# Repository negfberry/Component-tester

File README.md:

# Component-tester
Component tester for Arduino:

For documentation, see the Wiki.

Test many types of semiconductors, resistors, capacitors, inductors, etc.

Full list:

Resistors

Capacitors

Inductors

Diodes

Double diodes - common a/c, series, and inverse-parallel

Zener diodes

BJTs (Bipolar Junction Transistors):

    Regular
  
    Darlington pair
  
FETs:

    JFET
  
    MOSFET:
  
        enhancement mode
    
        depletion mode
    
IGBTs (Insulated Gate Bipolar Transistor)

Triacs

Thyristors

Based on Ardutester and earlier works. Uses the ButtonCtl Arduino library (in my Github). Includes hardware design schematic and PCB layout in Eagle format.
The DUT inputs are relay protected against charged capacitors being inserted.
Do not connect batteries or super capacitors.

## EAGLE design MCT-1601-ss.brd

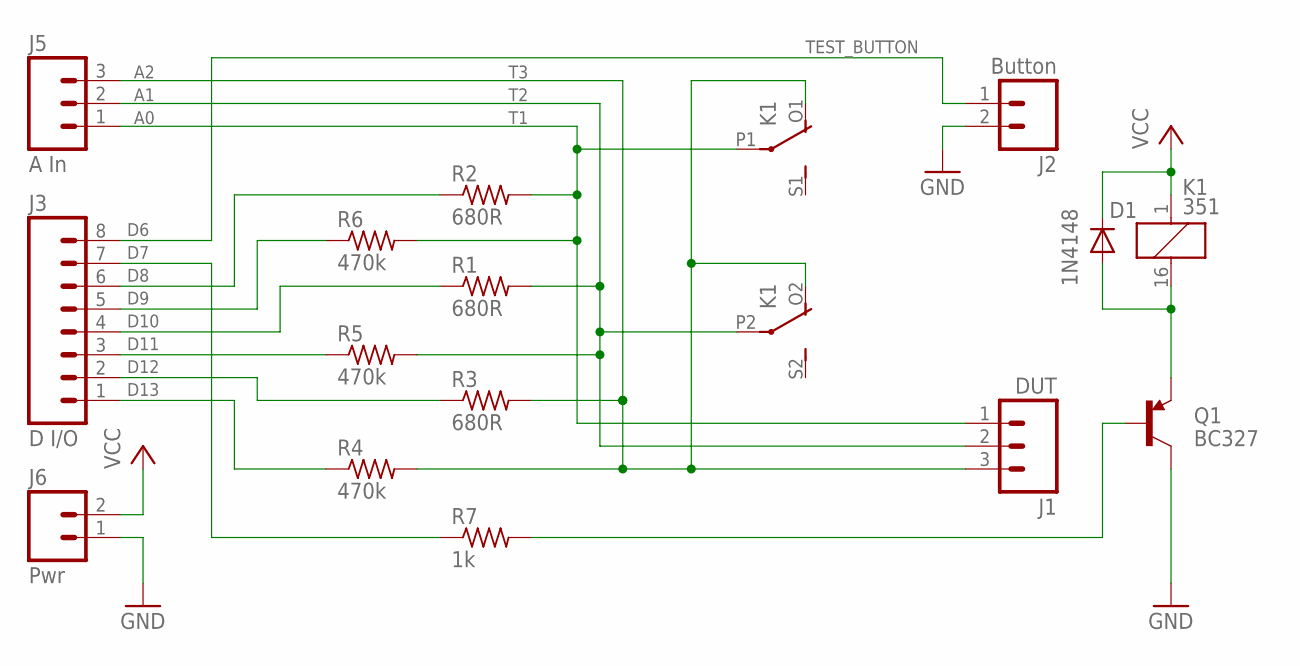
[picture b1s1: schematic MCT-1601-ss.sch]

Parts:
D1: 1N4148; D-2.5
J1: DUT; 1X03
J2: Button; 1X02
J3: D I/O; 1X08_ROUND
J5: A In; 1X03
J6: Pwr; 1X02
K1: 351
Q1: BC327; TO-92
R1, R2, R3: 680R; 0204/5
R4, R5, R6: 470k; 0204/5
R7: 1k; 0204/5

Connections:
D7: J3.7, R7.1
D8: J3.6, R2.1
D9: J3.5, R6.1
D10: J3.4, R1.1
D11: J3.3, R5.1
D12: J3.2, R3.1
D13: J3.1, R4.1
GND: J2.2, J6.1, Q1.3 (C)
unnamed: Q1.2 (B), R7.2
unnamed: D1.A, K1.16 (2), Q1.1 (E)
T1: J1.1, J5.1, K1.P1, R2.2, R6.2
T2: J1.2, J5.2, K1.P2, R1.2, R5.2
T3: J1.3, J5.3, K1.O1 (O), K1.O2 (O), R3.2, R4.2
TEST_BUTTON: J2.1, J3.8
VCC: D1.C, J6.2, K1.1

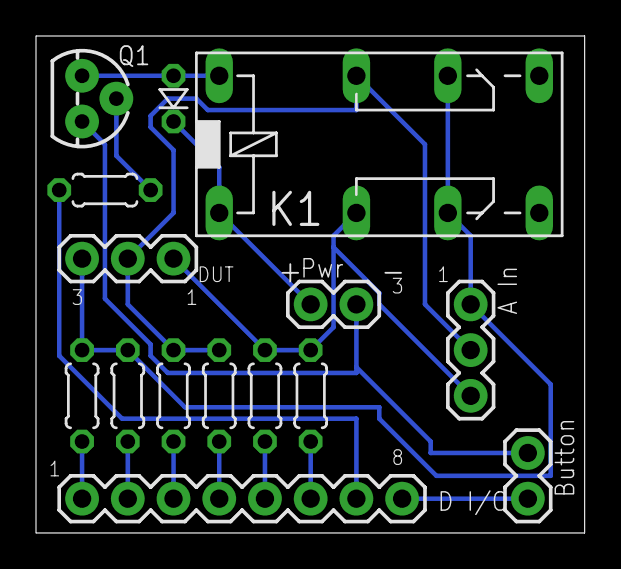
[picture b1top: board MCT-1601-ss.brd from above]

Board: 2 copper layers, 30.5 x 27.6 mm, 15 parts (0 on the bottom side), 15 nets.

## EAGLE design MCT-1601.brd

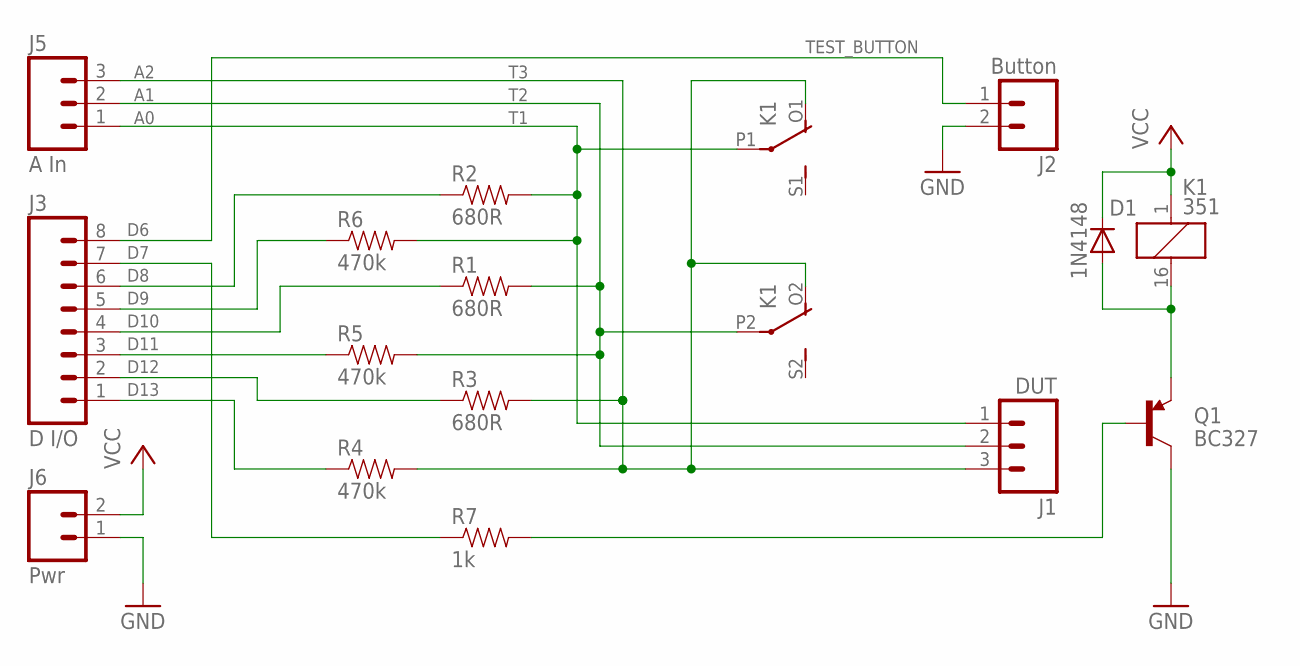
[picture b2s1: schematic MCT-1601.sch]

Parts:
D1: 1N4148; D-2.5
J1: DUT; 1X03
J2: Button; 1X02
J3: D I/O; 1X08_ROUND
J5: A In; 1X03
J6: Pwr; 1X02
K1: 351
Q1: BC327; TO-92
R1, R2, R3: 680R; AXIAL-0.1
R4, R5, R6: 470k; AXIAL-0.1
R7: 1k; AXIAL-0.1

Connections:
D7: J3.7, R7.P$1 (1)
D8: J3.6, R2.P$1 (1)
D9: J3.5, R6.P$1 (1)
D10: J3.4, R1.P$1 (1)
D11: J3.3, R5.P$1 (1)
D12: J3.2, R3.P$1 (1)
D13: J3.1, R4.P$1 (1)
GND: J2.2, J6.1, Q1.3 (C)
unnamed: Q1.2 (B), R7.P$2 (2)
unnamed: D1.A, K1.16 (2), Q1.1 (E)
T1: J1.1, J5.1, K1.P1, R2.P$2 (2), R6.P$2 (2)
T2: J1.2, J5.2, K1.P2, R1.P$2 (2), R5.P$2 (2)
T3: J1.3, J5.3, K1.O1 (O), K1.O2 (O), R3.P$2 (2), R4.P$2 (2)
TEST_BUTTON: J2.1, J3.8
VCC: D1.C, J6.2, K1.1

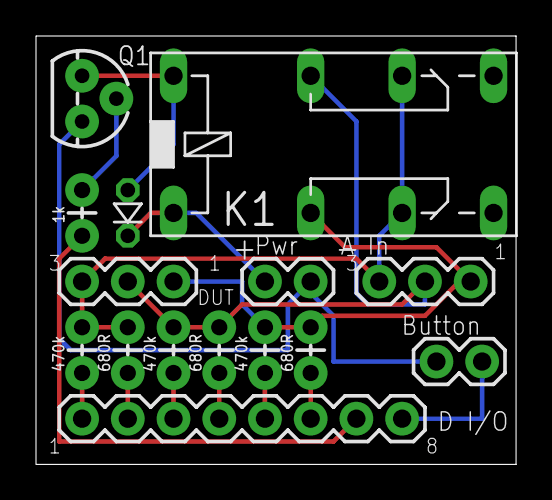
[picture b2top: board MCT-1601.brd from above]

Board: 2 copper layers, 26.7 x 23.8 mm, 15 parts (0 on the bottom side), 15 nets.

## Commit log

2016-08-23 Code clean-ups
2016-08-23 Add more detail
2016-08-23 More code cleanups
2016-08-23 More code cleanups, added continuous test mode
2016-08-23 fix booboo
2016-08-23 typo
2016-08-24 Renaming variables and functions, cleanup
2016-08-24 Added Darlinton support, Calibration cleanups, PROGMEM icon fixed
    Added a subtype field to the checks struct, and added subtypes 'TYPE_REGULAR' and 'TYPE_DARLINGTON' for BJTs. Added code to save and display this information.
    Made the Calibration functions much neater. Fixed up button presses when in Calibration mode.
    Fixed the generation of custom character icons from Flash, which was borked.
2016-08-24 Added full list, including Darlington pairs.
2016-08-24 Formatting
2016-08-25 Added reference to the Wiki
2016-08-25 Added startup diagnostics, more cleanups
2016-08-25 Modified to support autodiagnostics on startup
2016-08-25 Pictures of the PCB
2016-08-26 Adding correct ec2 verion
2016-08-26 Correct ec2 versions
2016-08-26 Added correct ec2 version - try 2
2016-08-29 Add Zener diodes
2016-08-29 Added double diode and Zener support
2016-08-30 Added extra diode support
2016-08-30 Fixed and enhanced diode display
2016-08-30 missing series type in double diode entry
2016-08-30 Thai-po
2016-08-31 Cleanups
2016-08-31 Slightly larger single-sided version of the PCB
2016-08-31 Added diode value
2016-08-31 Moved traces to bottom
2016-08-31 Slightly larger single sided
2016-08-31 Slightly larger single sided PCB
2016-08-31 reload

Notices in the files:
parts and their libraries:
SparkFun-Connectors: Licensing: Creative Commons ShareAlike 4.0 International - https://creativecommons.org/licenses/by-sa/4.0
